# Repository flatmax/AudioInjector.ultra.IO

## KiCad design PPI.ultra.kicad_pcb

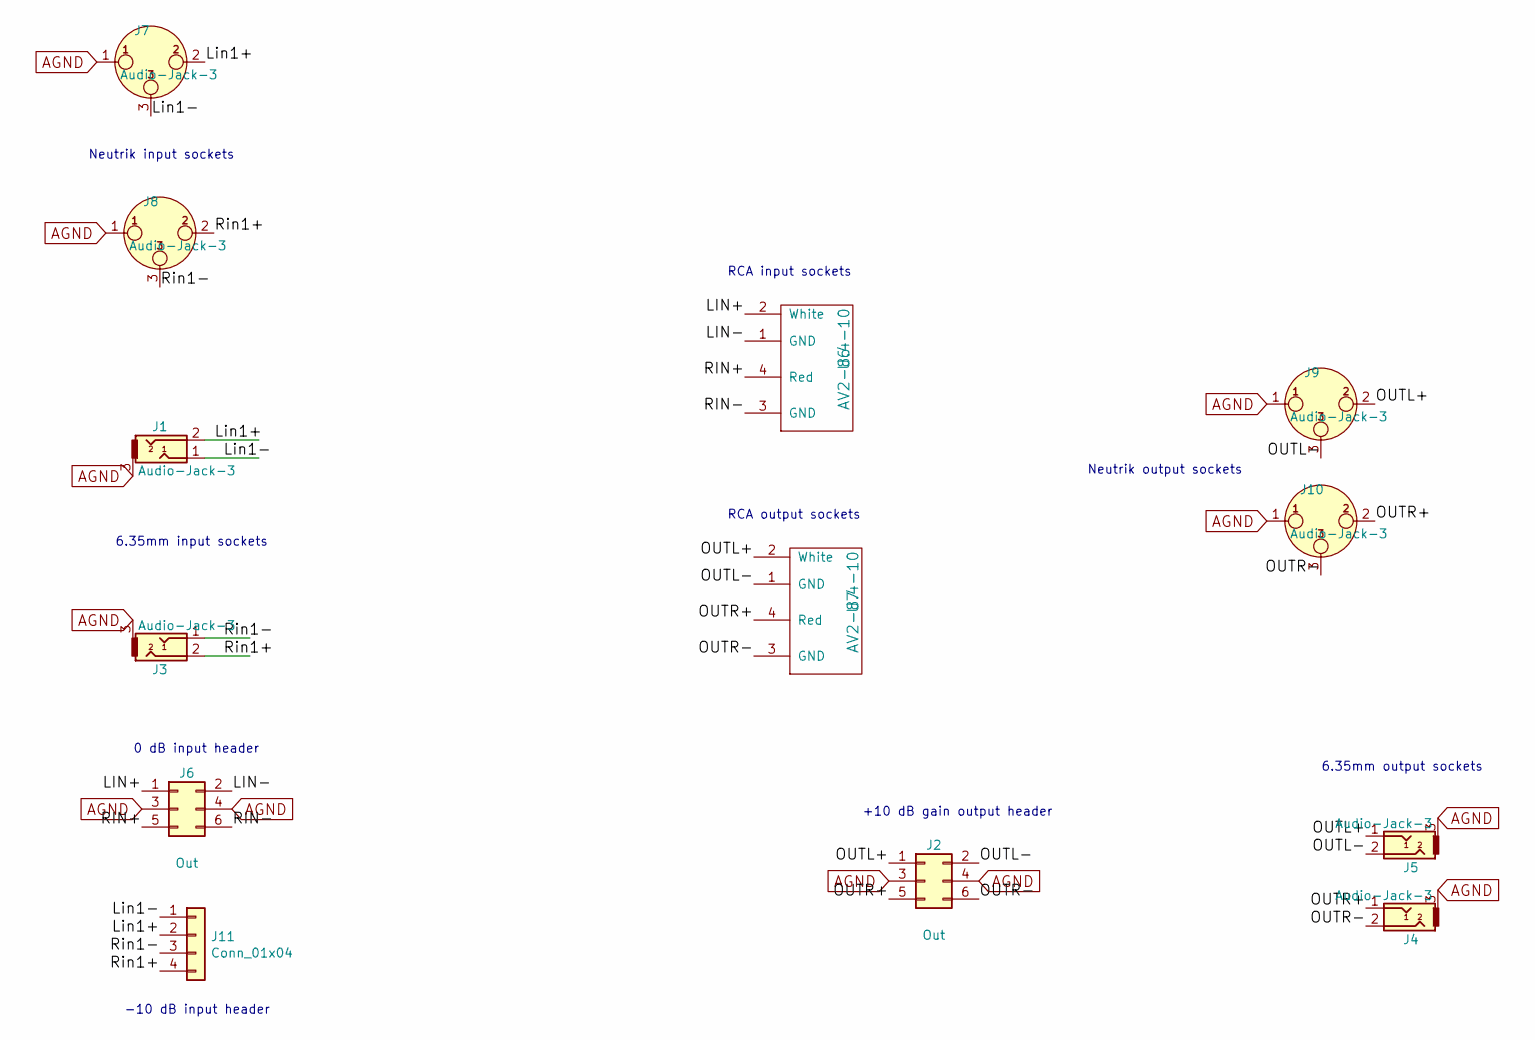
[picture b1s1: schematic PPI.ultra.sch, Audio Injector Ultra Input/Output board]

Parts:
J1, J3, J4, J5: Audio-Jack-3; 334g_6p
J2, J6: Out; Pin_Header_Straight_2x03_Pitch2.54mm
J7, J8: Audio-Jack-3; XLR-NC3FA
J9, J10: Audio-Jack-3; XLR-NC3MA
J11: Conn_01x04; PinHeader_1x04_P2.54mm_Vertical
U6, U7: AV2-8.4-10

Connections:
/LIN+: J6.1, U6.2 (White)
/LIN-: J6.2, U6.1 (GND)
/Lin1+: J1.2, J7.2, J11.2
/Lin1-: J1.1, J7.3, J11.1
/OUTL+: J2.1, J5.1, J9.2, U7.2 (White)
/OUTL-: J2.2, J5.2, J9.3, U7.1 (GND)
/OUTR+: J2.5, J4.1, J10.2, U7.4 (Red)
/OUTR-: J2.6, J4.2, J10.3, U7.3 (GND)
/RIN+: J6.5, U6.4 (Red)
/RIN-: J6.6, U6.3 (GND)
/Rin1+: J3.2, J8.2, J11.4
/Rin1-: J3.1, J8.3, J11.3
AGND: J1.3, J2.3, J2.4, J3.3, J4.3, J5.3, J6.3, J6.4, J7.1, J8.1, J9.1, J10.1

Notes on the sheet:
Neutrik input sockets
6.35mm input sockets
RCA input sockets
RCA output sockets
Neutrik output sockets
6.35mm output sockets
+10 dB gain output header
0 dB input header
-10 dB input header

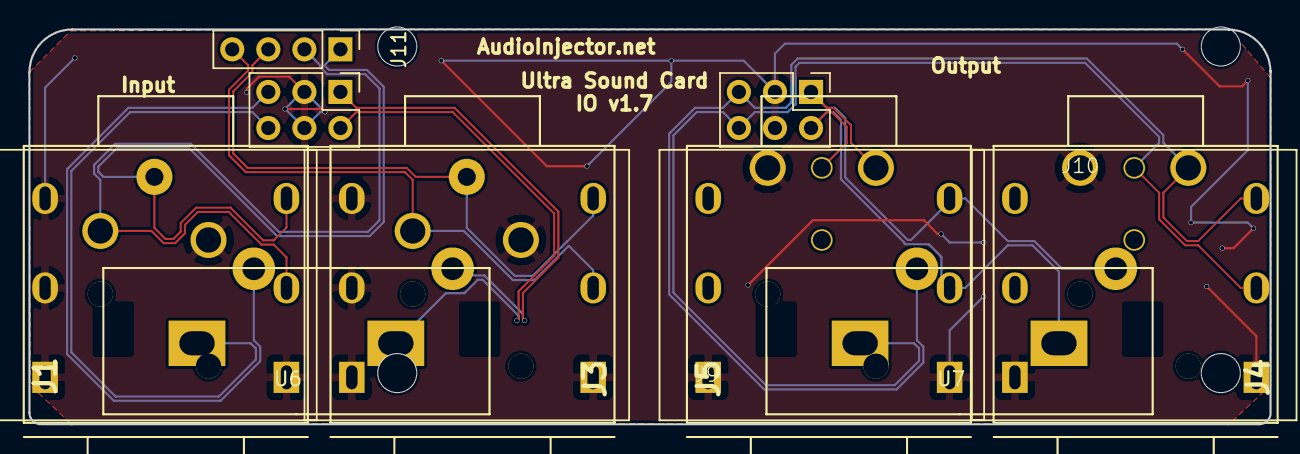
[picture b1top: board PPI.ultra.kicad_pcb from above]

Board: 2 copper layers, 87.4 x 27.8 mm, 17 parts (0 on the bottom side), 13 nets.

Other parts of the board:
1PIN, 1PIN#2, 1PIN#3, 1PIN#4: P***; 1pin
